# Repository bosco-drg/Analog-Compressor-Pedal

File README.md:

# Guitar Pedal — Analog Compressor

> Complete analog guitar compressor pedal project, including schematic and PCB design (KiCad) and simulations (LTSpice).

---

## Quick overview

This project designs and documents an **analog guitar compressor**: input/output adaptation, amplification, envelope detection, and gain control. It includes the **schematic**, **PCB**, as well as **simulations** and **test results**.

### Key features

- **Analog compression**: dynamic reduction of the audio signal
- **Complete signal chain**: input adaptation, amplification, peak detection, gain control, output adaptation
- **Hardware design**: schematic + PCB routing in KiCad
- **Simulation**: LTSpice models and sub‑block tests
- **Visual documentation**: block diagrams and simulation captures

---

## Circuit overview

<div align="center">

**Global diagram** — *Functional architecture of the pedal*

</div>

<div align="center">

**Global circuit** — *Schematic overview*

</div>

---

## Sub‑block details

### Input adaptation

<div align="center">

**Input adaptation** — *Guitar signal conditioning*

</div>

### Amplification

<div align="center">

**Amplification** — *Signal amplification stages*

</div>

### Peak detection / envelope

<div align="center">

**Peak detection** — *Envelope generation for control*

</div>

### Gain control / attenuation

<div align="center">

**Gain control** — *Envelope‑controlled attenuation*

</div>

### Output adaptation

<div align="center">

**Output adaptation** — *Compatibility with amp or audio interface*

</div>

---

## LTSpice simulations

<div align="center">

**Envelope simulation** — *Detection response*

</div>

<div align="center">

**Signal simulation** — *Compression effect on the signal*

</div>

---

## PCB — Photos

<div align="center">

**PCB back side**

</div>

<div align="center">

**PCB component side**

</div>

---

## Project structure

```
Analog-Compressor-Pedal/
├── README.md
├── doc/                       # Visual documentation and images
├── LTSpice/                   # Schematics and simulation tests
│   ├── Circuit_complet_avec_Adaptation.asc
│   ├── Audio Tests/
│   ├── Circuit Test Results/
│   └── PWL Sound Files/
└── pedaleGuitareComp/         # KiCad project (schematic + PCB)
		├── pedaleGuitareComp.kicad_sch
		├── pedaleGuitareComp.kicad_pcb
		└── footprints_perso/
```

---

## Open the project

### KiCad
- Open the project in [pedaleGuitareComp/](pedaleGuitareComp/)
- Main files:
	- Schematic: [pedaleGuitareComp/pedaleGuitareComp.kicad_sch](pedaleGuitareComp/pedaleGuitareComp.kicad_sch)
	- PCB: [pedaleGuitareComp/pedaleGuitareComp.kicad_pcb](pedaleGuitareComp/pedaleGuitareComp.kicad_pcb)

### LTSpice
- Full schematic: [LTSpice/Circuit_complet_avec_Adaptation.asc](LTSpice/Circuit_complet_avec_Adaptation.asc)
- Tests and results: [LTSpice/](LTSpice/)

---

## Authors

- **Bosco de Rauglaudre**
- **Titouan Bocquet**
- **Gavin Mac Aonghusa**

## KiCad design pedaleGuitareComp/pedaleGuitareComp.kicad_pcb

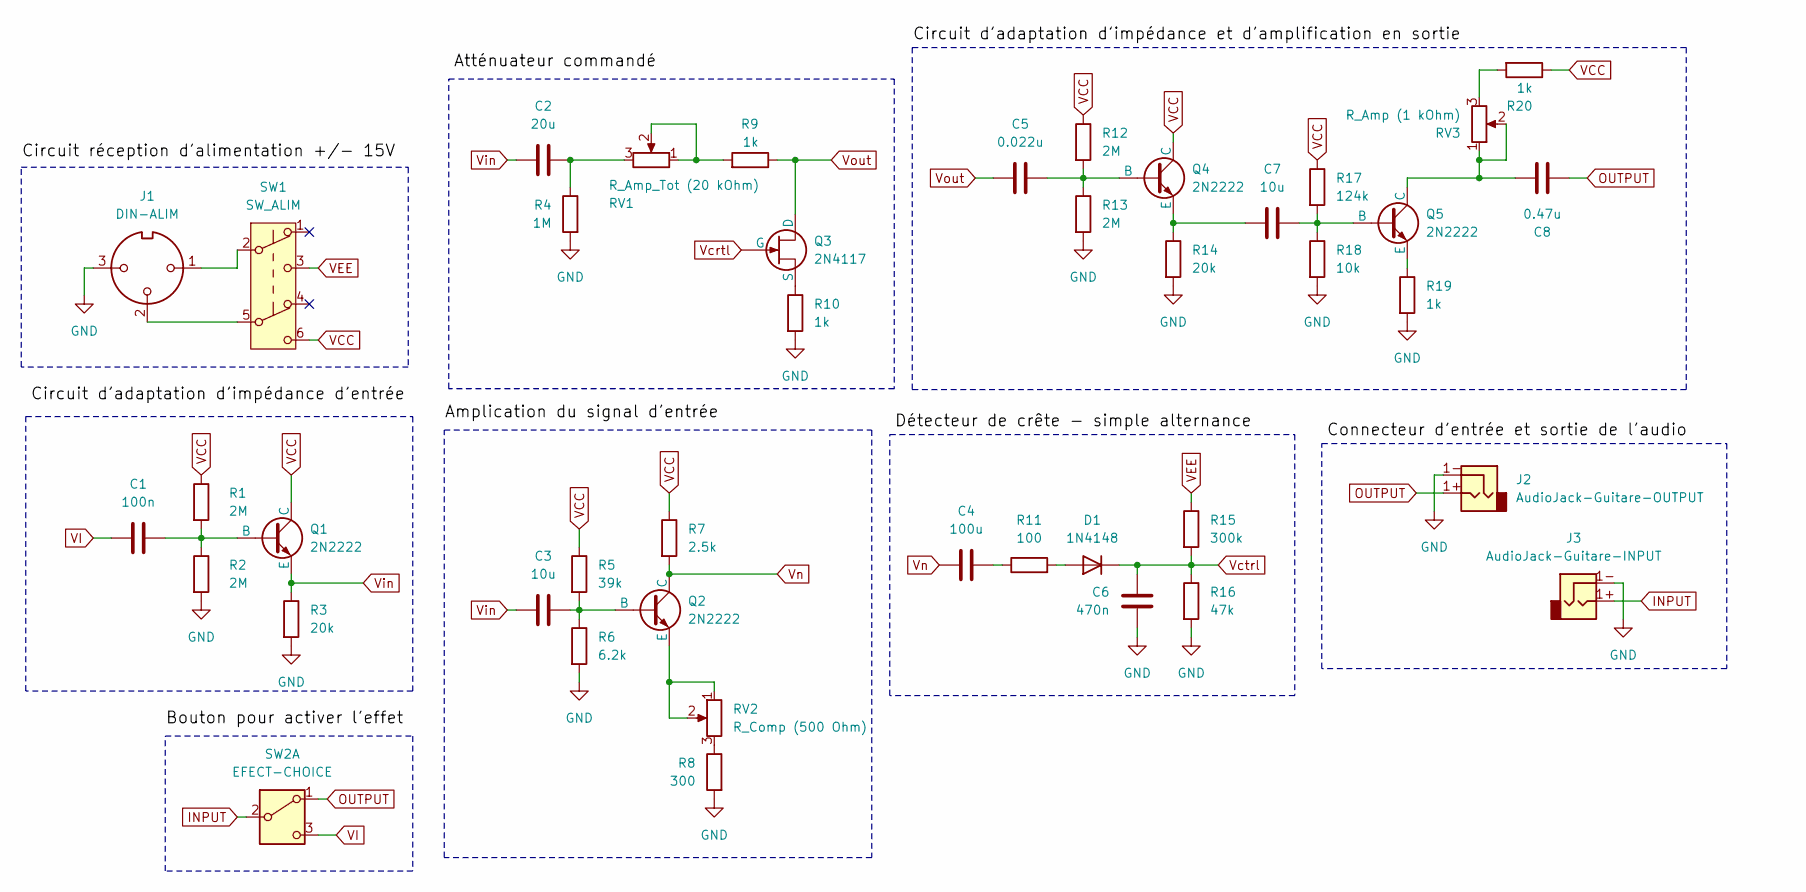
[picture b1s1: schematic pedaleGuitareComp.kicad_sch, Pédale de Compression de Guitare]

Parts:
C1: 100n; C_Disc_D5.0mm_W2.5mm_P5.00mm
C2: 20u; CP_Radial_D6.3mm_P2.50mm
C3, C7: 10u; CP_Radial_D6.3mm_P2.50mm
C4: 100u; CP_Radial_D6.3mm_P2.50mm
C5: 0.022u; C_Rect_L7.2mm_W2.5mm_P5.00mm
C6: 470n; C_Rect_L7.2mm_W2.5mm_P5.00mm
C8: 0.47u; C_Rect_L7.2mm_W2.5mm_P5.00mm
D1: 1N4148; D_DO-35_SOD27_P7.62mm_Horizontal
J1: DIN-ALIM; TerminalBlock_Phoenix_MKDS-1,5-3_1x03_P5.00mm_Horizontal
J2: AudioJack-Guitare-OUTPUT; Jack_speakON-6.35mm_Neutrik_NLJ2MDXX-H_Horizontal
J3: AudioJack-Guitare-INPUT; Jack_speakON-6.35mm_Neutrik_NLJ2MDXX-H_Horizontal
Q1, Q2, Q4, Q5: 2N2222; TO-92_Inline
Q3: 2N4117; TO-92_Inline
R1, R2, R12, R13: 2M; R_Axial_DIN0207_L6.3mm_D2.5mm_P7.62mm_Horizontal
R3, R14: 20k; R_Axial_DIN0207_L6.3mm_D2.5mm_P7.62mm_Horizontal
R4: 1M; R_Axial_DIN0207_L6.3mm_D2.5mm_P7.62mm_Horizontal
R5: 39k; R_Axial_DIN0207_L6.3mm_D2.5mm_P7.62mm_Horizontal
R6: 6.2k; R_Axial_DIN0207_L6.3mm_D2.5mm_P7.62mm_Horizontal
R7: 2.5k; R_Axial_DIN0207_L6.3mm_D2.5mm_P7.62mm_Horizontal
R8: 300; R_Axial_DIN0207_L6.3mm_D2.5mm_P7.62mm_Horizontal
R9, R10, R19, R20: 1k; R_Axial_DIN0207_L6.3mm_D2.5mm_P7.62mm_Horizontal
R11: 100; R_Axial_DIN0207_L6.3mm_D2.5mm_P7.62mm_Horizontal
R15: 300k; R_Axial_DIN0207_L6.3mm_D2.5mm_P7.62mm_Horizontal
R16: 47k; R_Axial_DIN0207_L6.3mm_D2.5mm_P7.62mm_Horizontal
R17: 124k; R_Axial_DIN0207_L6.3mm_D2.5mm_P7.62mm_Horizontal
R18: 10k; R_Axial_DIN0207_L6.3mm_D2.5mm_P7.62mm_Horizontal
RV1: R_Amp_Tot (20 kOhm); PinHeader_1x03_P2.54mm_Vertical
RV2: R_Comp (500 Ohm); PinHeader_1x03_P2.54mm_Vertical
RV3: R_Amp (1 kOhm); PinHeader_1x03_P2.54mm_Vertical
SW1: SW_ALIM; SW_E-Switch_EG1271_SPDT
SW2: EFECT-CHOICE; PinHeader_1x03_P2.54mm_Vertical

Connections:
GND: C6.2, J1.3, J2.1-, J3.1-, R2.2, R3.2, R4.2, R6.2, R8.2, R10.2, R13.2, R14.2, R16.2, R18.2, R19.2
INPUT: J3.1+, SW2.2 (B)
unnamed: C2.2, R4.1, RV1.3
unnamed: C4.1, R11.1
unnamed: D1.2 (A), R11.2
unnamed: J1.1, SW1.2 (B)
unnamed: J1.2, SW1.5 (B)
unnamed: C1.1, Q1.2 (B), R1.2, R2.1
unnamed: C3.2, Q2.2 (B), R5.2, R6.1
unnamed: Q2.3 (E), RV2.1, RV2.2
unnamed: Q3.3 (S), R10.1
unnamed: C5.1, Q4.2 (B), R12.2, R13.1
unnamed: C7.1, Q4.3 (E), R14.1
unnamed: C7.2, Q5.2 (B), R17.2, R18.1
unnamed: C8.1, Q5.1 (C), RV3.1, RV3.2
unnamed: Q5.3 (E), R19.1
unnamed: R8.1, RV2.3
unnamed: R9.2, RV1.1, RV1.2
unnamed: R20.2, RV3.3
OUTPUT: C8.2, J2.1+, SW2.1 (A)
VCC: Q1.1 (C), Q4.1 (C), R1.1, R5.1, R7.1, R12.1, R17.1, R20.1, SW1.6 (C)
VEE: R15.1, SW1.3 (C)
VI: C1.2, SW2.3 (C)
Vcrtl: Q3.2 (G)
Vctrl: C6.1, D1.1 (K), R15.2, R16.1
Vin: C2.1, C3.1, Q1.3 (E), R3.1
Vn: C4.2, Q2.1 (C), R7.2
Vout: C5.2, Q3.1 (D), R9.1

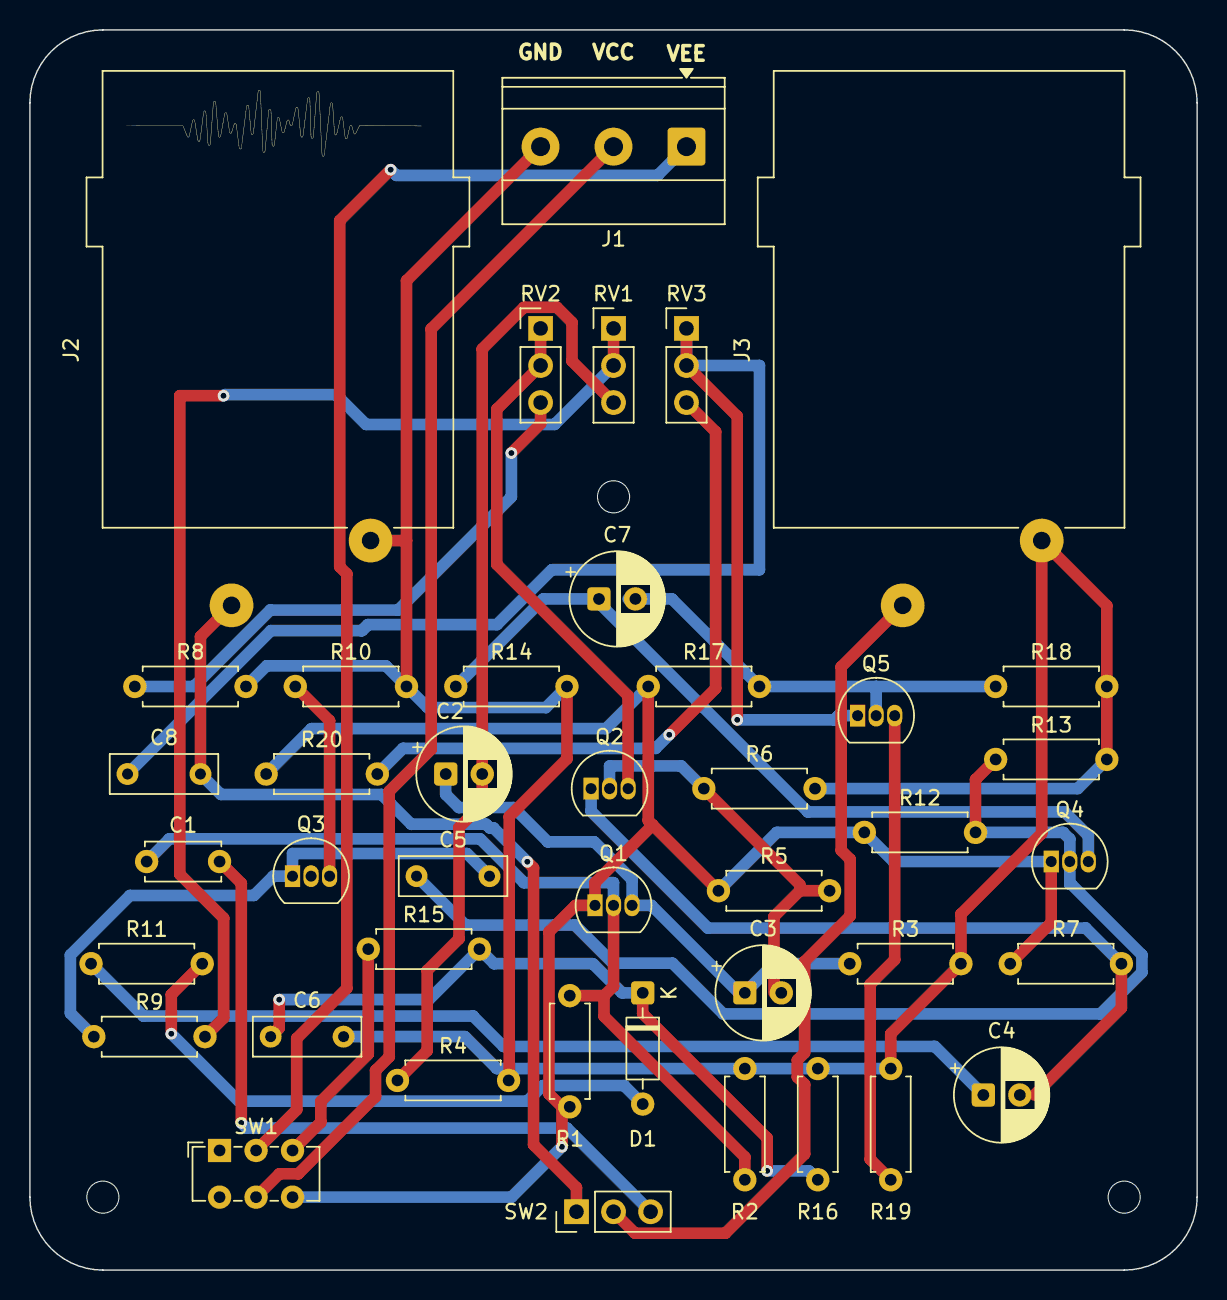
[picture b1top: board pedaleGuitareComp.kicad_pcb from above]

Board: 2 copper layers, 80.0 x 85.0 mm, 42 parts (0 on the bottom side), 27 nets.

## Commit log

2026-02-04 push complet du projet
